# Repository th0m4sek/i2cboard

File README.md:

SSR board based on pcf8574 and G3mc

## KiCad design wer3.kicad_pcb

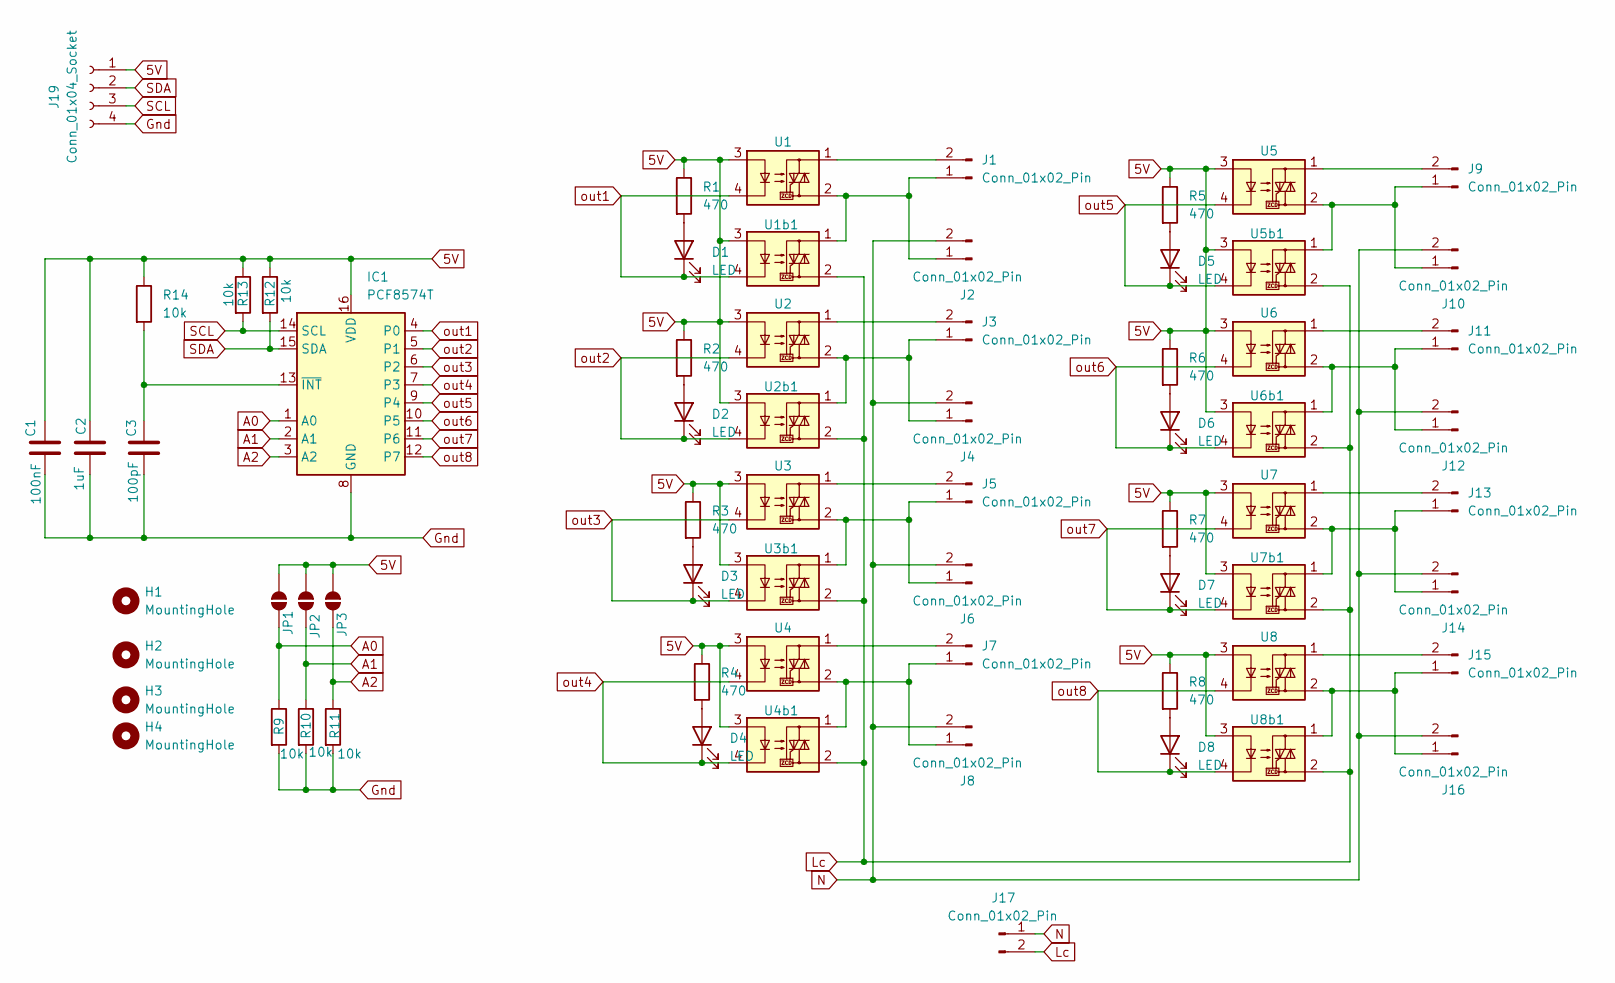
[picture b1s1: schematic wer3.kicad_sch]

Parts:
C1: 100nF; C_0603_1608Metric
C2: 1uF; C_0603_1608Metric
C3: 100pF; C_0603_1608Metric
D1, D2, D3, D4, D5, D6, D7, D8: LED; LED_0603_1608Metric
H1, H2, H3, H4: MountingHole; MountingHole_3.2mm_M3
IC1: PCF8574T; SOIC-16W_7.5x10.3mm_P1.27mm
J1, J2, J3, J4, J5, J6, J7, J8, J9, J10, J11, J12, J13, J14, J15, J16, J17: Conn_01x02_Pin; PhoenixContact_MSTBA_2,5_2-G-5,08_1x02_P5.08mm_Horizontal
J19: Conn_01x04_Socket; PhoenixContact_MSTBA_2,5_4-G-5,08_1x04_P5.08mm_Horizontal
JP1, JP2, JP3: SolderJumper_2_Open; SolderJumper-2_P1.3mm_Open_RoundedPad1.0x1.5mm
R1, R2, R3, R4, R5, R6, R7, R8: 470; R_0603_1608Metric
R9, R10, R11, R12, R13, R14: 10k; R_0603_1608Metric
U1, U1b1, U2, U2b1, U3, U3b1, U4, U4b1, U5, U5b1, U6, U6b1, U7, U7b1, U8, U8b1: S102S02; G3MB-202P

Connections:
5V: C1.1, C2.1, IC1.16 (VDD), J19.1, JP1.2 (B), JP2.2 (B), JP3.2 (B), R1.1, R2.1, R3.1, R4.1, R5.1, R6.1, R7.1, R8.1, R12.1, R13.1, R14.1, U1.3, U1b1.3, U2.3, U2b1.3, U3.3, U3b1.3, U4.3, U4b1.3, U5.3, U5b1.3, U6.3, U6b1.3, U7.3, U7b1.3, U8.3, U8b1.3
A0: IC1.1 (A0), JP1.1 (A), R9.1
A1: IC1.2 (A1), JP2.1 (A), R10.1
A2: IC1.3 (A2), JP3.1 (A), R11.1
Gnd: C1.2, C2.2, C3.2, IC1.8 (GND), J19.4, R9.2, R10.2, R11.2
Lc: J17.2, U1b1.2, U2b1.2, U3b1.2, U4b1.2, U5b1.2, U6b1.2, U7b1.2, U8b1.2
N: J2.2, J4.2, J6.2, J8.2, J10.2, J12.2, J14.2, J16.2, J17.1
unnamed: D1.2 (A), R1.2
unnamed: D2.2 (A), R2.2
unnamed: D3.2 (A), R3.2
unnamed: D4.2 (A), R4.2
unnamed: D5.2 (A), R5.2
unnamed: D6.2 (A), R6.2
unnamed: D7.2 (A), R7.2
unnamed: D8.2 (A), R8.2
unnamed: C3.1, IC1.13 (~INT), R14.2
unnamed: J1.1, J2.1, U1.2, U1b1.1
unnamed: J1.2, U1.1
unnamed: J3.1, J4.1, U2.2, U2b1.1
unnamed: J3.2, U2.1
unnamed: J5.1, J6.1, U3.2, U3b1.1
unnamed: J5.2, U3.1
unnamed: J7.1, J8.1, U4.2, U4b1.1
unnamed: J7.2, U4.1
unnamed: J9.2, U5.1
unnamed: J9.1, J10.1, U5.2, U5b1.1
unnamed: J11.1, J12.1, U6.2, U6b1.1
unnamed: J11.2, U6.1
unnamed: J13.1, J14.1, U7.2, U7b1.1
unnamed: J13.2, U7.1
unnamed: J15.1, J16.1, U8.2, U8b1.1
unnamed: J15.2, U8.1
SCL: IC1.14 (SCL), J19.3, R13.2
SDA: IC1.15 (SDA), J19.2, R12.2
out1: D1.1 (K), IC1.4 (P0), U1.4, U1b1.4
out2: D2.1 (K), IC1.5 (P1), U2.4, U2b1.4
out3: D3.1 (K), IC1.6 (P2), U3.4, U3b1.4
out4: D4.1 (K), IC1.7 (P3), U4.4, U4b1.4
out5: D5.1 (K), IC1.9 (P4), U5.4, U5b1.4
out6: D6.1 (K), IC1.10 (P5), U6.4, U6b1.4
out7: D7.1 (K), IC1.11 (P6), U7.4, U7b1.4
out8: D8.1 (K), IC1.12 (P7), U8.4, U8b1.4

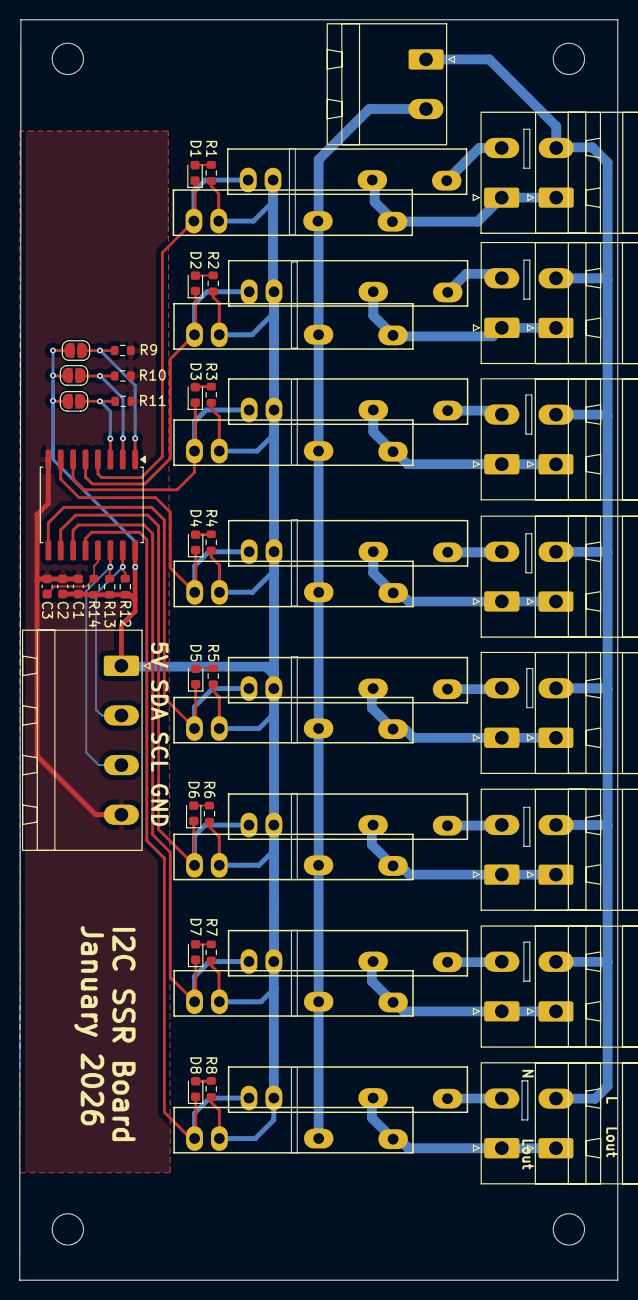
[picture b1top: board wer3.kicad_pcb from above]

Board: 2 copper layers, 61.2 x 129.0 mm, 67 parts (0 on the bottom side), 42 nets.
